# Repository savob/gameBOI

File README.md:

# gameBOI

My first personal circuit board project which I took on sort of like a hackathon to get done fast so I could show potential employers in the summer of 2019. Designed, ordered, assembled, programmed and debugged in the space of two weeks! Unfotunately I didn't get to show it off much given my limited number of interviews, but still proud of it.

*I initially forgot to buy one SMD resistor, so had to use a through-hole one.* 

## Hardware

The design is pretty simple looking back, basically the heart of an Arduino Nano with four shift registers daisy-chained to control the LEDs on board. There are two buttons for user input and two rows of 16 LEDs each resulting in the games and UI/UX being pretty simplistic. Power was supplied through a 9V battery that hung off the board going through a linear regulator.

I made two versions of the design, and commited to having the second built and assembled.

## Firmware

By replicating the heart of an Arduino Nano on the board, I could program it just like one through the Arduino IDE. One however was that instead of using a USB-UART interface and the Optiboot bootloader to program the chip, I used the AVR-ISP interface using an Arduino Uno as an ISP.

My code organization was pretty simple and I tried to make it easily scalable. I decided early on that I would make a seperate file for each sort of "stage" the user was in, so `mainmenu` and one for each different game (e.g. `stacker`), as well as one for all the shared functions like updating the screen so they could be maintained easier. *I now realize that what I had accidentally created was a Finite State Machine (FSM), and a project specific library.*

## Software Used

The board was designed in EAGLE (based on release dates, probably v9.4.0). Code was written in the Arduino IDE v1.8.9.

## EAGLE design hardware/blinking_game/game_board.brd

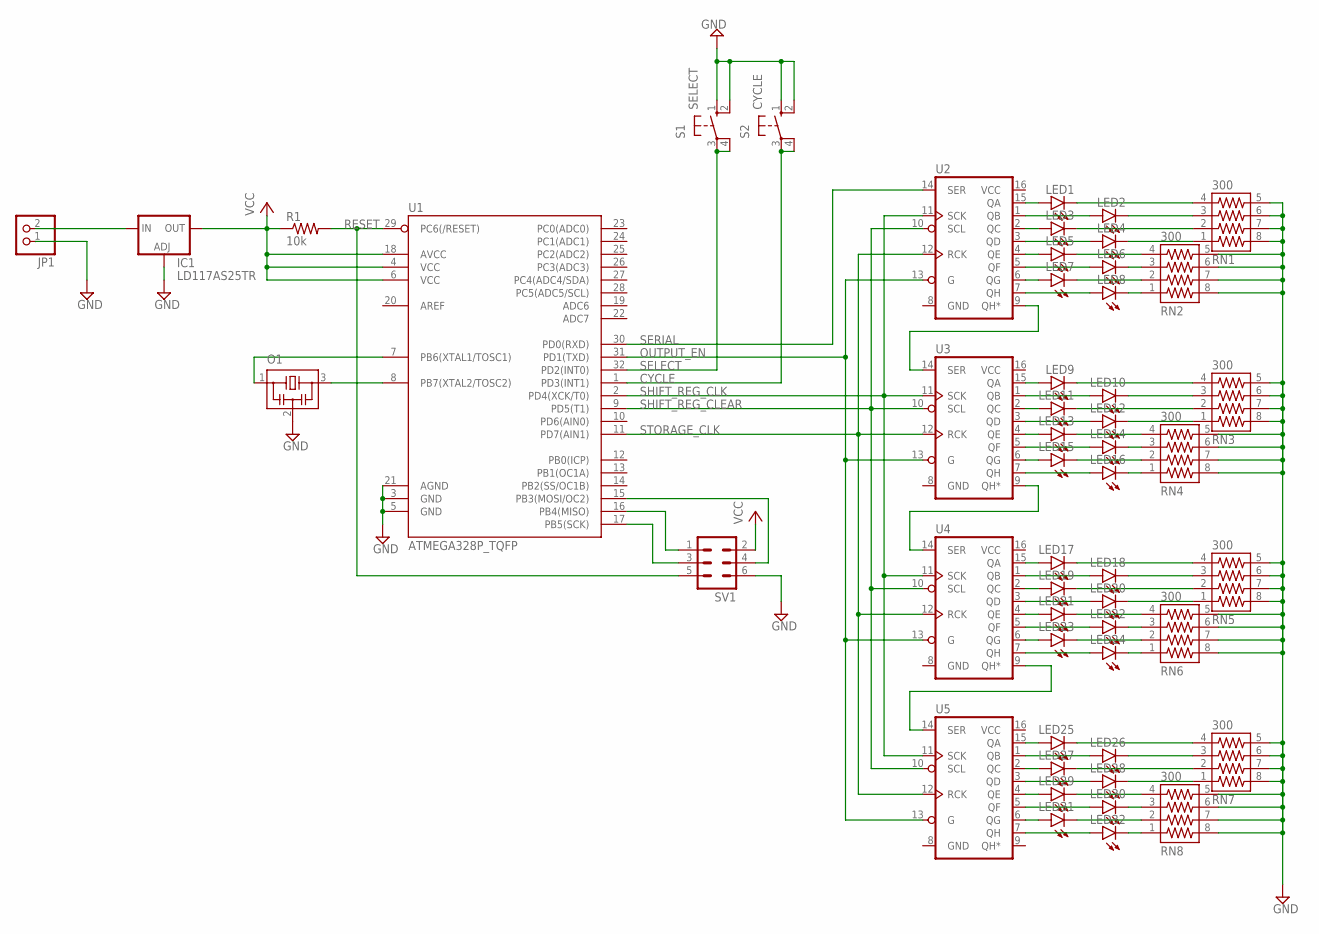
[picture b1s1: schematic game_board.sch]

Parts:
IC1: LD117AS25TR; SOT223
JP1: PINHD-1X2; 1X02
LED1, LED2, LED3, LED4, LED5, LED6, LED7, LED8, LED9, LED10, LED11, LED12, LED13, LED14, LED15, LED16, LED17, LED18, LED19, LED20, LED21, LED22, LED23, LED24, LED25, LED26, LED27, LED28, LED29, LED30, LED31, LED32: LEDSML0805; SML0805
O1: CSTNE16M0V530000R0; CSTCR6M
R1: 10k; R0603
RN1, RN2, RN3, RN4, RN5, RN6, RN7, RN8: 300; RESCAXS80P320X250X60-8
S1: SELECT; B3F-10XX
S2: CYCLE; B3F-10XX
SV1: MA03-2
U1: ATMEGA328P_TQFP; TQFP32-08
U2, U3, U4, U5: 74595; TSSOP16

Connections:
CYCLE: S2.3, S2.4 (P1), U1.1 (PD3(INT1))
GND: IC1.1 (ADJ), JP1.1, O1.2, RN1.5, RN1.6, RN1.7, RN1.8, RN2.5, RN2.6, RN2.7, RN2.8, RN3.5, RN3.6, RN3.7, RN3.8, RN4.5, RN4.6, RN4.7, RN4.8, RN5.5, RN5.6, RN5.7, RN5.8, RN6.5, RN6.6, RN6.7, RN6.8, RN7.5, RN7.6, RN7.7, RN7.8, RN8.5, RN8.6, RN8.7, RN8.8, S1.1 (S), S1.2 (S1), S2.1 (S), S2.2 (S1), SV1.6, U1.3 (GND), U1.5 (GND), U1.21 (AGND), U2.8 (GND), U3.8 (GND), U4.8 (GND), U5.8 (GND)
MISO: SV1.1, U1.16 (PB4(MISO))
MOSI: SV1.4, U1.15 (PB3(MOSI/OC2))
unnamed: O1.1, U1.7 (PB6(XTAL1/TOSC1))
unnamed: O1.3, U1.8 (PB7(XTAL2/TOSC2))
unnamed: LED17.A, U4.15 (QA)
unnamed: LED18.A, U4.1 (QB)
unnamed: LED17.C, RN5.4
unnamed: LED18.C, RN5.3
unnamed: U3.9 (QH*), U4.14 (SER)
unnamed: U2.9 (QH*), U3.14 (SER)
unnamed: U4.9 (QH*), U5.14 (SER)
unnamed: LED1.A, U2.15 (QA)
unnamed: LED2.A, U2.1 (QB)
unnamed: LED1.C, RN1.4
unnamed: LED2.C, RN1.3
unnamed: LED3.A, U2.2 (QC)
unnamed: LED3.C, RN1.2
unnamed: LED4.C, RN1.1
unnamed: LED4.A, U2.3 (QD)
unnamed: LED5.A, U2.4 (QE)
unnamed: LED6.A, U2.5 (QF)
unnamed: LED5.C, RN2.4
unnamed: LED6.C, RN2.3
unnamed: LED7.C, RN2.2
unnamed: LED7.A, U2.6 (QG)
unnamed: LED8.A, U2.7 (QH)
unnamed: LED8.C, RN2.1
unnamed: LED9.A, U3.15 (QA)
unnamed: LED10.A, U3.1 (QB)
unnamed: LED9.C, RN3.4
unnamed: LED10.C, RN3.3
unnamed: LED11.A, U3.2 (QC)
unnamed: LED11.C, RN3.2
unnamed: LED12.C, RN3.1
unnamed: LED12.A, U3.3 (QD)
unnamed: LED13.A, U3.4 (QE)
unnamed: LED14.A, U3.5 (QF)
unnamed: LED13.C, RN4.4
unnamed: LED14.C, RN4.3
unnamed: LED15.C, RN4.2
unnamed: LED15.A, U3.6 (QG)
unnamed: LED16.A, U3.7 (QH)
unnamed: LED16.C, RN4.1
unnamed: LED19.A, U4.2 (QC)
unnamed: LED19.C, RN5.2
unnamed: LED20.C, RN5.1
unnamed: LED20.A, U4.3 (QD)
unnamed: LED21.A, U4.4 (QE)
unnamed: LED22.A, U4.5 (QF)
unnamed: LED21.C, RN6.4
unnamed: LED22.C, RN6.3
unnamed: LED23.C, RN6.2
unnamed: LED23.A, U4.6 (QG)
unnamed: LED24.A, U4.7 (QH)
unnamed: LED24.C, RN6.1
unnamed: LED25.A, U5.15 (QA)
unnamed: LED26.A, U5.1 (QB)
unnamed: LED25.C, RN7.4
unnamed: LED26.C, RN7.3
unnamed: LED27.A, U5.2 (QC)
unnamed: LED27.C, RN7.2
unnamed: LED28.C, RN7.1
unnamed: LED28.A, U5.3 (QD)
unnamed: LED29.A, U5.4 (QE)
unnamed: LED30.A, U5.5 (QF)
unnamed: LED29.C, RN8.4
unnamed: LED30.C, RN8.3
unnamed: LED31.C, RN8.2
unnamed: LED31.A, U5.6 (QG)
unnamed: LED32.A, U5.7 (QH)
unnamed: LED32.C, RN8.1
unnamed: IC1.3 (IN), JP1.2
OUTPUT_EN: U1.31 (PD1(TXD)), U2.13 (G), U3.13 (G), U4.13 (G), U5.13 (G)
RESET: R1.2, SV1.5, U1.29 (PC6(/RESET))
SCK: SV1.3, U1.17 (PB5(SCK))
SELECT: S1.3, S1.4 (P1), U1.32 (PD2(INT0))
SERIAL: U1.30 (PD0(RXD)), U2.14 (SER)
SHIFT_REG_CLEAR: U1.9 (PD5(T1)), U2.10 (SCL), U3.10 (SCL), U4.10 (SCL), U5.10 (SCL)
SHIFT_REG_CLK: U1.2 (PD4(XCK/T0)), U2.11 (SCK), U3.11 (SCK), U4.11 (SCK), U5.11 (SCK)
STORAGE_CLK: U1.11 (PD7(AIN1)), U2.12 (RCK), U3.12 (RCK), U4.12 (RCK), U5.12 (RCK)
VCC: IC1.4 (OUT), R1.1, SV1.2, U1.4 (VCC), U1.6 (VCC), U1.18 (AVCC), U2.16 (VCC), U3.16 (VCC), U4.16 (VCC), U5.16 (VCC)

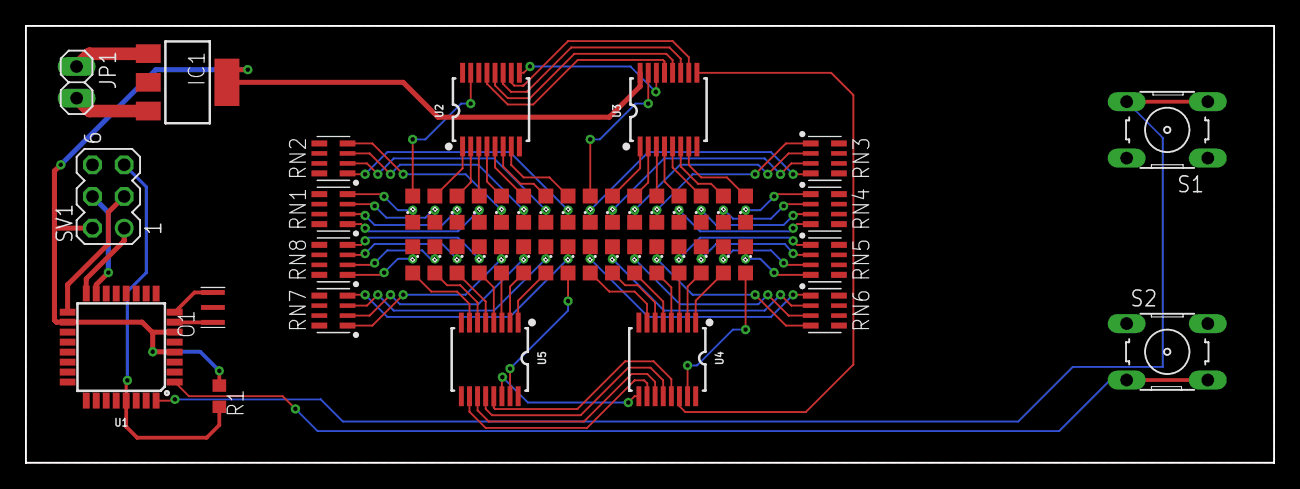
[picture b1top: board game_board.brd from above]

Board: 2 copper layers, 100.0 x 35.0 mm, 52 parts (0 on the bottom side), 83 nets.

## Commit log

2021-03-08 Initial
2024-01-04 Uploading PDF manual
2024-01-04 Removed precompiled binary files
2024-01-04 Added image to readme
2024-01-04 Uploaded hardware original files
2024-01-04 Moved firmware into appropriate folder

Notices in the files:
parts and their libraries:
SparkFun-IC-Microcontroller: Licensing: Creative Commons ShareAlike 4.0 International - https://creativecommons.org/licenses/by-sa/4.0
